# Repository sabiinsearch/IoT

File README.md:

## IoT
Infomation related to Internet of Things (I of Things)

## Code
    - include coding part

## Design
    - include GUI(external) and PCB designs

##  Projects
  - Includes Projects with Internet Of Things

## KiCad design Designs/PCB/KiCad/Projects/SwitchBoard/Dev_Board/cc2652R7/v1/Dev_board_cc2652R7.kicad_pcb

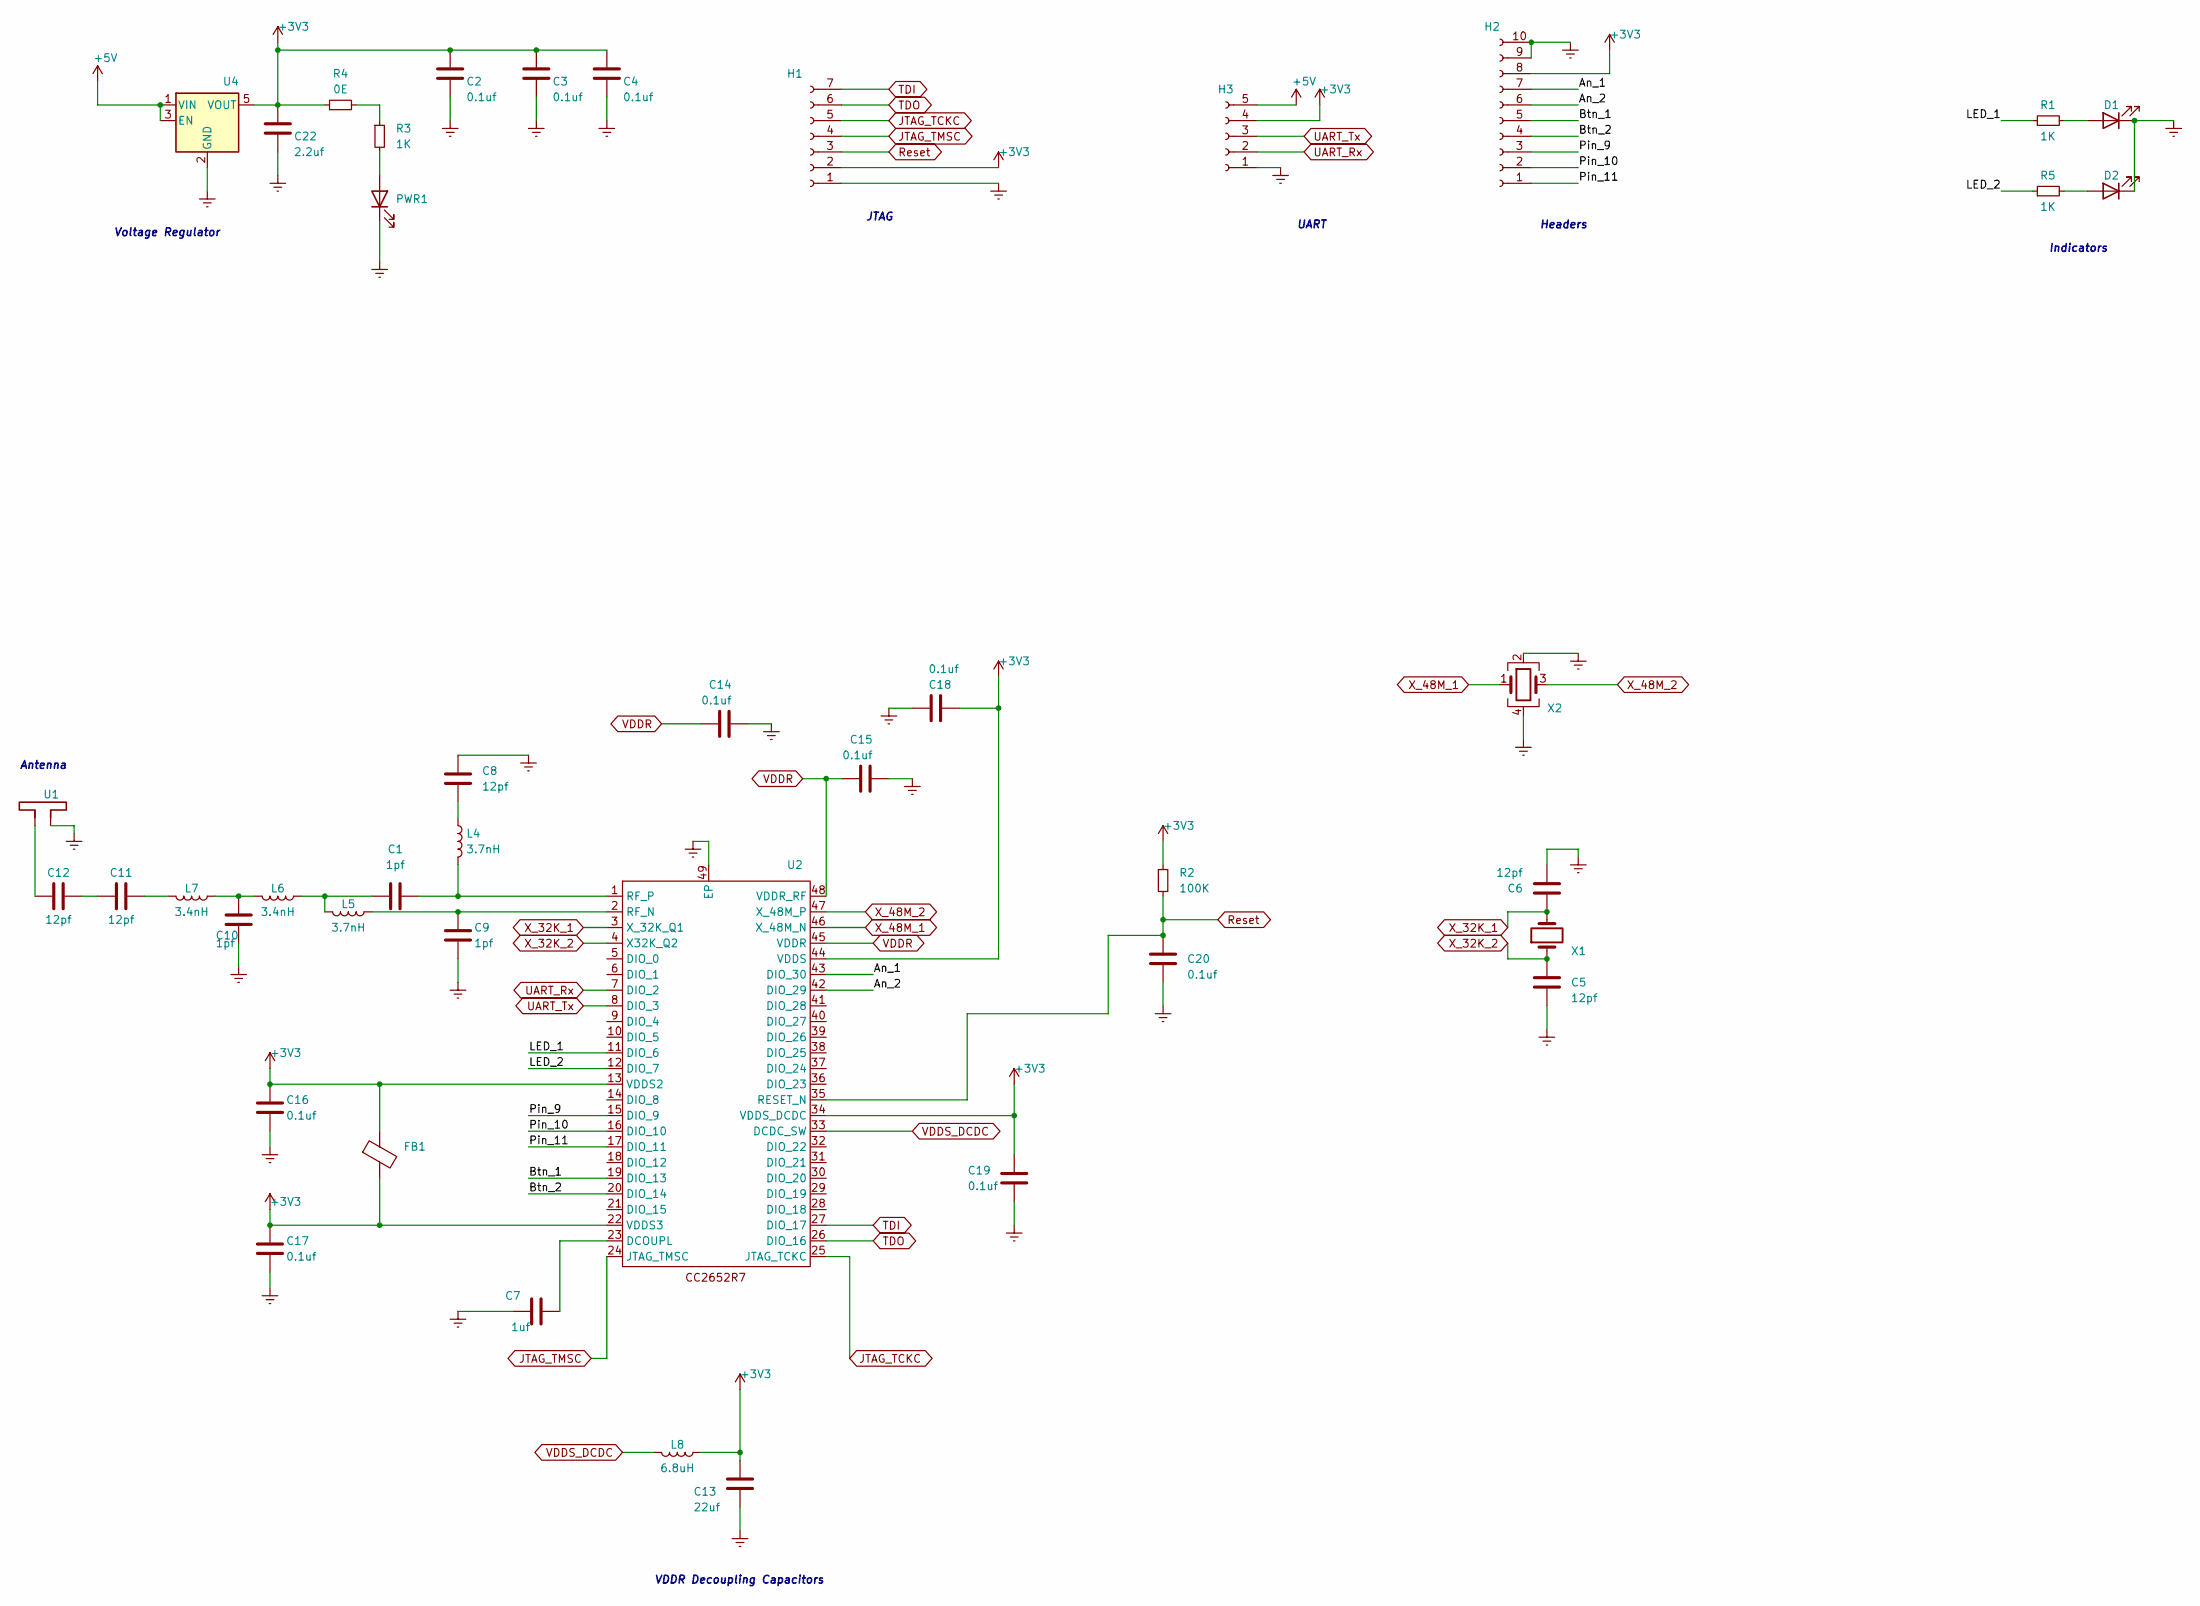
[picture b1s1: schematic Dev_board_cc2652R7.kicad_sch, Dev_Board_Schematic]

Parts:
C1, C9, C10: 1pf; C_0603_1608Metric_Pad1.08x0.95mm_HandSolder
C2, C3, C4, C14, C15, C16, C17, C18, C19, C20: 0.1uf; C_0603_1608Metric_Pad1.08x0.95mm_HandSolder
C5, C6, C8, C11, C12: 12pf; C_0603_1608Metric_Pad1.08x0.95mm_HandSolder
C7: 1uf; C_0603_1608Metric_Pad1.08x0.95mm_HandSolder
C13: 22uf; C_0603_1608Metric_Pad1.08x0.95mm_HandSolder
C22: 2.2uf; C_0603_1608Metric_Pad1.08x0.95mm_HandSolder
D1: LED_1; LED_0603_1608Metric_Pad1.05x0.95mm_HandSolder
D2: LED_2; LED_0603_1608Metric_Pad1.05x0.95mm_HandSolder
FB1: FerriteBead; R_0805_2012Metric_Pad1.20x1.40mm_HandSolder
H1: JTAG_Conn; PinHeader_1x07_P2.54mm_Vertical
H2: Headers; PinHeader_1x10_P2.54mm_Vertical
H3: UART_Conn; PinHeader_1x05_P2.54mm_Vertical
L4, L5: 3.7nH; L_0603_1608Metric_Pad1.05x0.95mm_HandSolder
L6, L7: 3.4nH; L_0603_1608Metric_Pad1.05x0.95mm_HandSolder
L8: 6.8uH; L_0603_1608Metric_Pad1.05x0.95mm_HandSolder
PWR1: LED; LED_0603_1608Metric_Pad1.05x0.95mm_HandSolder
R1, R3, R5: 1K; R_0603_1608Metric_Pad0.98x0.95mm_HandSolder
R2: 100K; R_0603_1608Metric_Pad0.98x0.95mm_HandSolder
R4: 0E; R_0603_1608Metric_Pad0.98x0.95mm_HandSolder
U1: Antenna_Dipole; Texas_SWRA117D_2.4GHz_Left
U2: cc2652R7
U4: AP2112K-3.3; SOT-23-5
X1: 32.768KHz; Crystal_C38-LF_D3.0mm_L8.0mm_Vertical
X2: 48MHz; Crystal_SMD_0603-4Pin_6.0x3.5mm_HandSoldering

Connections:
+3V3: C2.1, C3.1, C4.1, C13.1, C16.1, C17.1, C18.1, C19.1, C22.1, FB1.1, FB1.2, H1.2, H2.8, H3.4, L8.1, R2.1, R4.1, U2.13 (VDDS2), U2.22 (VDDS3), U2.34 (VDDS_DCDC), U2.44 (VDDS), U4.5 (VOUT)
+5V: H3.5, U4.1 (VIN), U4.3 (EN)
/An_1: H2.7, U2.43 (DIO_30)
/An_2: H2.6, U2.42 (DIO_29)
/Btn_1: H2.5, U2.19 (DIO_13)
/Btn_2: H2.4, U2.20 (DIO_14)
/LED_1: R1.1, U2.11 (DIO_6)
/LED_2: R5.1, U2.12 (DIO_7)
/Pin_9: H2.3, U2.15 (DIO_9)
/Pin_10: H2.2, U2.16 (DIO_10)
/Pin_11: H2.1, U2.17 (DIO_11)
GNDREF: C2.2, C3.2, C4.2, C5.2, C6.2, C7.1, C8.1, C9.2, C10.2, C13.2, C14.2, C15.2, C16.2, C17.2, C18.2, C19.2, C20.2, C22.2, D1.1 (K), D2.1 (K), H1.1, H2.9, H2.10, H3.1, PWR1.1 (K), U1.2, U2.49 (EP), U4.2 (GND), X2.2, X2.4; also elsewhere on the board
JTAG_TCKC: H1.5, U2.25 (JTAG_TCKC)
JTAG_TMSC: H1.4, U2.24 (JTAG_TMSC)
unnamed: C1.1, L5.2, L6.1
unnamed: C8.2, L4.1
unnamed: C10.1, L6.2, L7.1
unnamed: C11.1, C12.2
unnamed: C11.2, L7.2
unnamed: C12.1, U1.1
unnamed: D1.2 (A), R1.2
unnamed: D2.2 (A), R5.2
unnamed 22: PWR1.2 (A), R3.2; also elsewhere on the board
unnamed: R3.1, R4.2
unnamed: C7.2, U2.23 (DCOUPL)
unnamed: C9.1, L5.1, U2.2 (RF_N)
unnamed: C1.2, L4.2, U2.1 (RF_P)
Reset: C20.1, H1.3, R2.2, U2.35 (RESET_N)
TDI: H1.7, U2.27 (DIO_17)
TDO: H1.6, U2.26 (DIO_16)
UART_Rx: H3.2, U2.7 (DIO_2)
UART_Tx: H3.3, U2.8 (DIO_3)
VDDR: C14.1, C15.1, U2.45 (VDDR), U2.48 (VDDR_RF)
VDDS_DCDC: L8.2, U2.33 (DCDC_SW)
X_32K_1: C6.1, U2.3 (X_32K_Q1), X1.2
X_32K_2: C5.1, U2.4 (X32K_Q2), X1.1
X_48M_1: U2.46 (X_48M_N), X2.1
X_48M_2: U2.47 (X_48M_P), X2.3

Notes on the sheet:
Antenna
JTAG
VDDR Decoupling Capacitors
Headers
Voltage Regulator
Indicators
UART

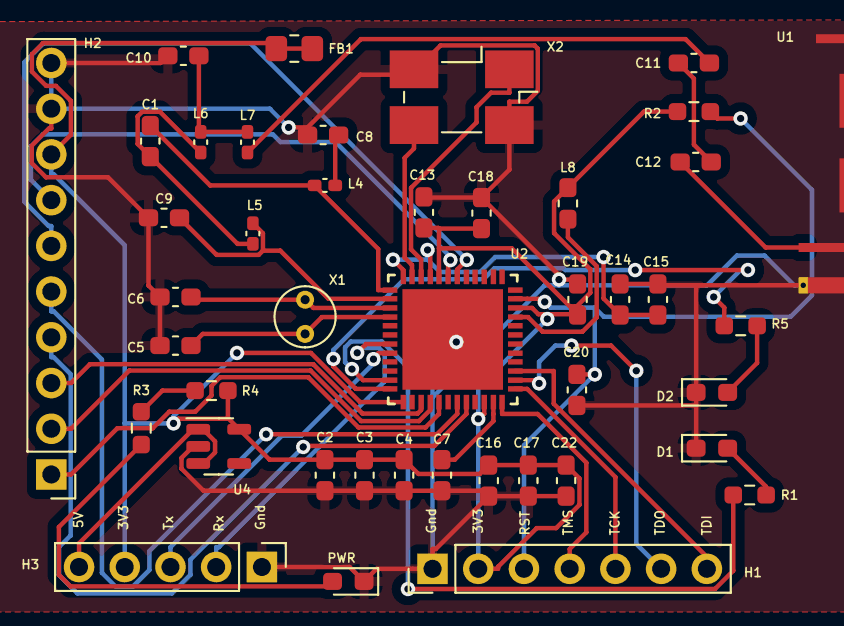
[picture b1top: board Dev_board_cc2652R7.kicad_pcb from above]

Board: 2 copper layers, 43 parts (0 on the bottom side), 38 nets.

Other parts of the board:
PWR: LED; LED_0603_1608Metric_Pad1.05x0.95mm_HandSolder

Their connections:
GNDREF: PWR.1 (K); also elsewhere on the board
unnamed 22: PWR.2 (A); also elsewhere on the board

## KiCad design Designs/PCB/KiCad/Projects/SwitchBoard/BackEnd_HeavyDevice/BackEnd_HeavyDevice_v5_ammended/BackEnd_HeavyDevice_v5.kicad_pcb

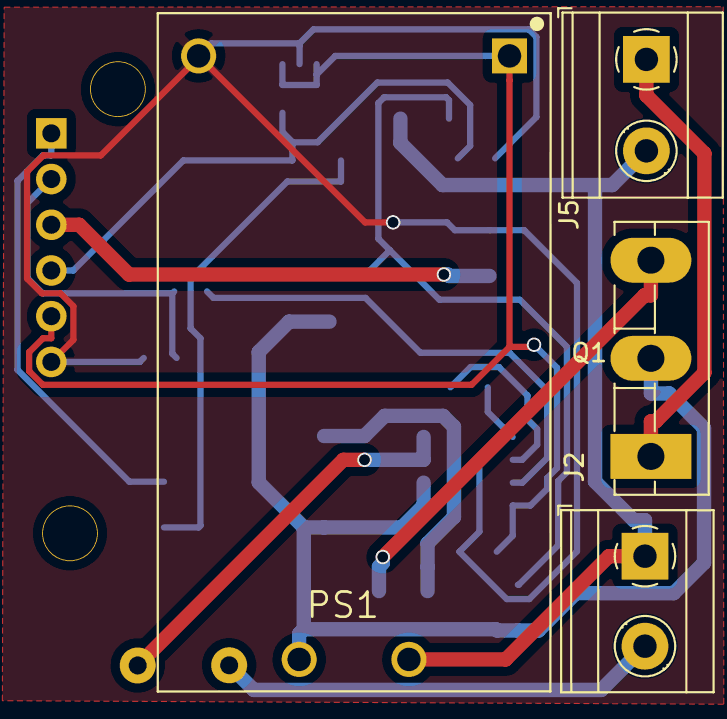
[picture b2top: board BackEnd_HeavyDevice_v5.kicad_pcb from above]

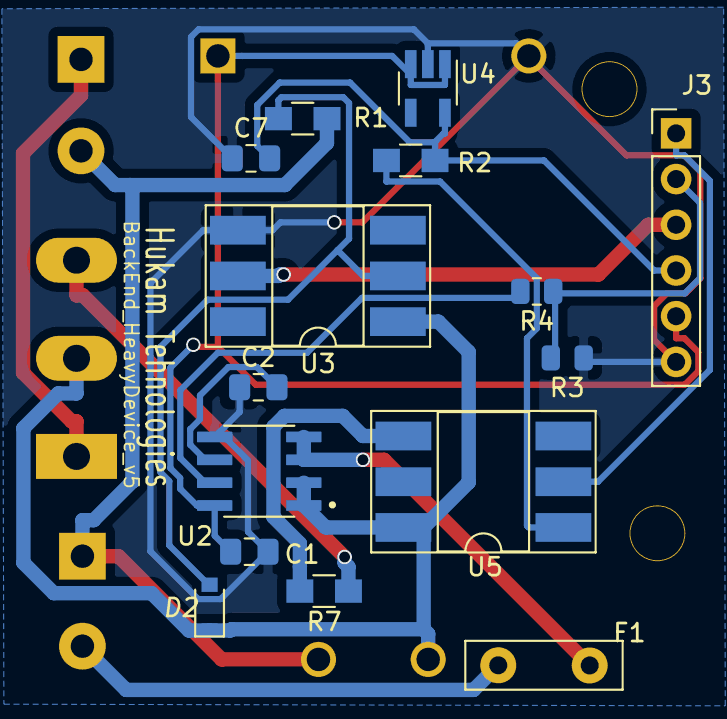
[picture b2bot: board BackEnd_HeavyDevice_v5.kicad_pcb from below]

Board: 2 copper layers, 21 parts (15 on the bottom side), 17 nets.

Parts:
C1: 100nf; C_0805_2012Metric_Pad1.18x1.45mm_HandSolder
C2: 1nf; C_0805_2012Metric_Pad1.18x1.45mm_HandSolder
C7: 2.2uf; C_0805_2012Metric_Pad1.18x1.45mm_HandSolder
D2: IN14007; D_0805
F1: Fuse_Small; Fuse_TE5_Littlefuse-395Series
J2: Screw_Terminal_01x02; TerminalBlock_Phoenix_MKDS-1,5-2_1x02_P5.00mm_Horizontal
J3: Conn_01x06_Female; PinHeader_1x06_P2.54mm_Vertical
J5: Screw_Terminal_01x02; TerminalBlock_Phoenix_MKDS-1,5-2-5.08_1x02_P5.08mm_Horizont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
M1, M2: MountingHole_2.1mm; MountingHole_2.5mm
PS1: HLK-PM01; 277
Q1: BT136-500; GN27120BN
R1: 220K; R_0805_HandSoldering
R2: 100E; R_0805_HandSoldering
R3, R4: 5K; R_0805_2012Metric
R7: 470E; R_0805_HandSoldering
U2: ACS712-20; ACS712_20
U3: 4N35; DIP-6_W8.89mm_SMDSocket_LongPads
U4: AP2112K-3.3; SOT-23-5_HandSoldering
U5: MOC3021; DIP-6_W8.89mm_SMDSocket_LongPads

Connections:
/3.3V: C7.2, J3.4, R2.2, U4.5
/5V: C1.1, J3.5, PS1.5, U2.8, U4.1, U4.3
/DSW1: J3.1, U5.2
/Energy_frmSensor: R4.2, U2.7
/Energy_toStm: J3.2, R3.2, R4.1
/GND: C1.2, C2.1, C7.1, J3.6, PS1.4, R3.1, U2.5, U3.4, U4.2
/Mains_Live_In: F1.1, J2.2
/Mains_Live_Out: D2.1, PS1.2, Q1.2, U2.1, U2.2, U3.1, U5.6
/Mains_Neutral: J2.1, J5.2, PS1.1, R1.2
/Opto_In: J3.3, U3.5
/Out1: J5.1, Q1.1
unnamed: C2.2, U2.6
unnamed: D2.2, R1.1, U3.2
unnamed: F1.2, U2.3, U2.4
unnamed: Q1.3, R7.1
unnamed: R2.1, U5.1
unnamed: R7.2, U5.4

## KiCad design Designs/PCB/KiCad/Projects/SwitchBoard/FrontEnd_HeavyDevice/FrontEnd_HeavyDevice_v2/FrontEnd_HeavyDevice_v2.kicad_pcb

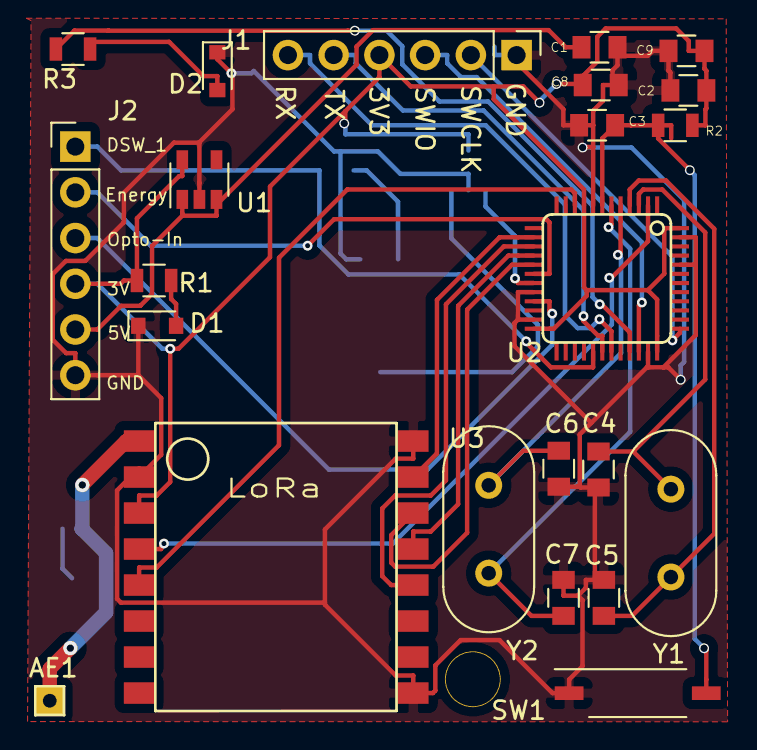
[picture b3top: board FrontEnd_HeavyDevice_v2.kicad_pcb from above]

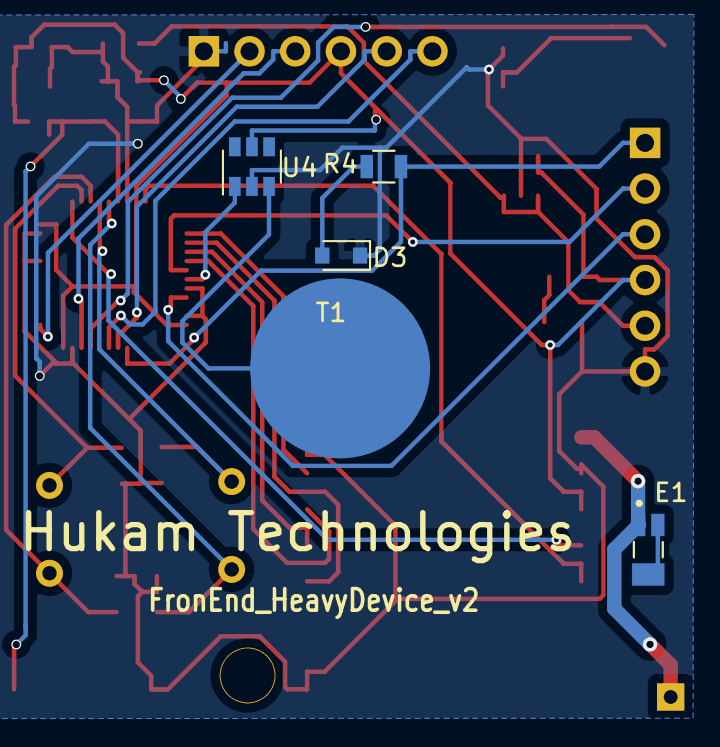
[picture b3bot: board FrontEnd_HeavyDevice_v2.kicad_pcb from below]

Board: 2 copper layers, 29 parts (5 on the bottom side), 29 nets.

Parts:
AE1: Antenna; Anntenna
C1, C2, C8: 100 nf; C_0805
C3: 1.0uf; C_0805
C4, C5: 10pf; C_0805
C6, C7: 20pf; C_0805
C9: 10uf; C_0805
D1, D2, D3: LED; D_0805
E1: YC0009AA; XCVR_YC0009AA
J1: Conn_01x06_Female; Pin_Header_Straight_1x06_Pitch2.54mm
J2: Conn_01x06_Female; PinHeader_1x06_P2.54mm_Vertical
M2: MountingHole_2.1mm; MountingHole_2.5mm
R1, R3, R4: 510 R; R_0805
R2: 10K; R_0805
SW1: SW_Push; SW_DIP_x1_W7.62mm_Slide_Copal_CHS-B
T1: Touch_Pad
U1: APK2112.K-3.3; SOT-23-5
U2: STM32; STM32(LQFP48)
U3: LoRa
U4: TTP223; SOT-23-6
Y1: 32.768K; Crystal_HC49-4H_Vertical
Y2: 32Mhz; Crystal_HC49-4H_Vertical

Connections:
/5V: C1.2, J2.5, U1.1, U1.3
/DIO0: U2.10, U3.5
/DSW_1: J2.1, R4.2, U2.29
/Energy: J2.2, U2.18
/GND: C1.1, C2.1, C3.1, C4.2, C5.2, C6.2, C7.2, C8.1, C9.1, D1.1, D2.1, D3.1, J1.1, J2.6, SW1.1, U1.2, U2.8, U2.20, U2.23, U2.35, U2.44, U2.47, U3.2, U3.9, U3.16, U4.2
/MISO: U2.16, U3.13
/MOSI: U2.17, U3.14
/NSS: U2.14, U3.15
/OSCIN: C6.1, U2.5, Y2.1
/OSCOUT: C7.1, U2.6, Y2.2
/Opto_IN: J2.3, U2.21
/PC14: C4.1, U2.3, Y1.1
/PC15: C5.1, U2.4, Y1.2
/RESET: C3.2, R2.2, SW1.2, U2.7
/RX0: J1.6, U2.31
/Reset_Lora: U2.2, U3.4
/SCK: U2.15, U3.12
/SWCLK: J1.2, U2.37
/SWIO: J1.3, U2.34
/TX0: J1.5, U2.30
/Touch_1: U2.19, U4.1
/VCC3V3: C2.2, C8.2, C9.2, J1.4, J2.4, R1.2, R2.1, U1.5, U2.9, U2.24, U2.36, U2.48, U3.3, U4.5
unnamed: AE1.1, E1.1, U3.1
unnamed: D1.2, R1.1
unnamed: D2.2, R3.1
unnamed: D3.2, R4.1
unnamed: E1.2, E1.3
unnamed: R3.2, U2.33
unnamed: T1.1, U4.3

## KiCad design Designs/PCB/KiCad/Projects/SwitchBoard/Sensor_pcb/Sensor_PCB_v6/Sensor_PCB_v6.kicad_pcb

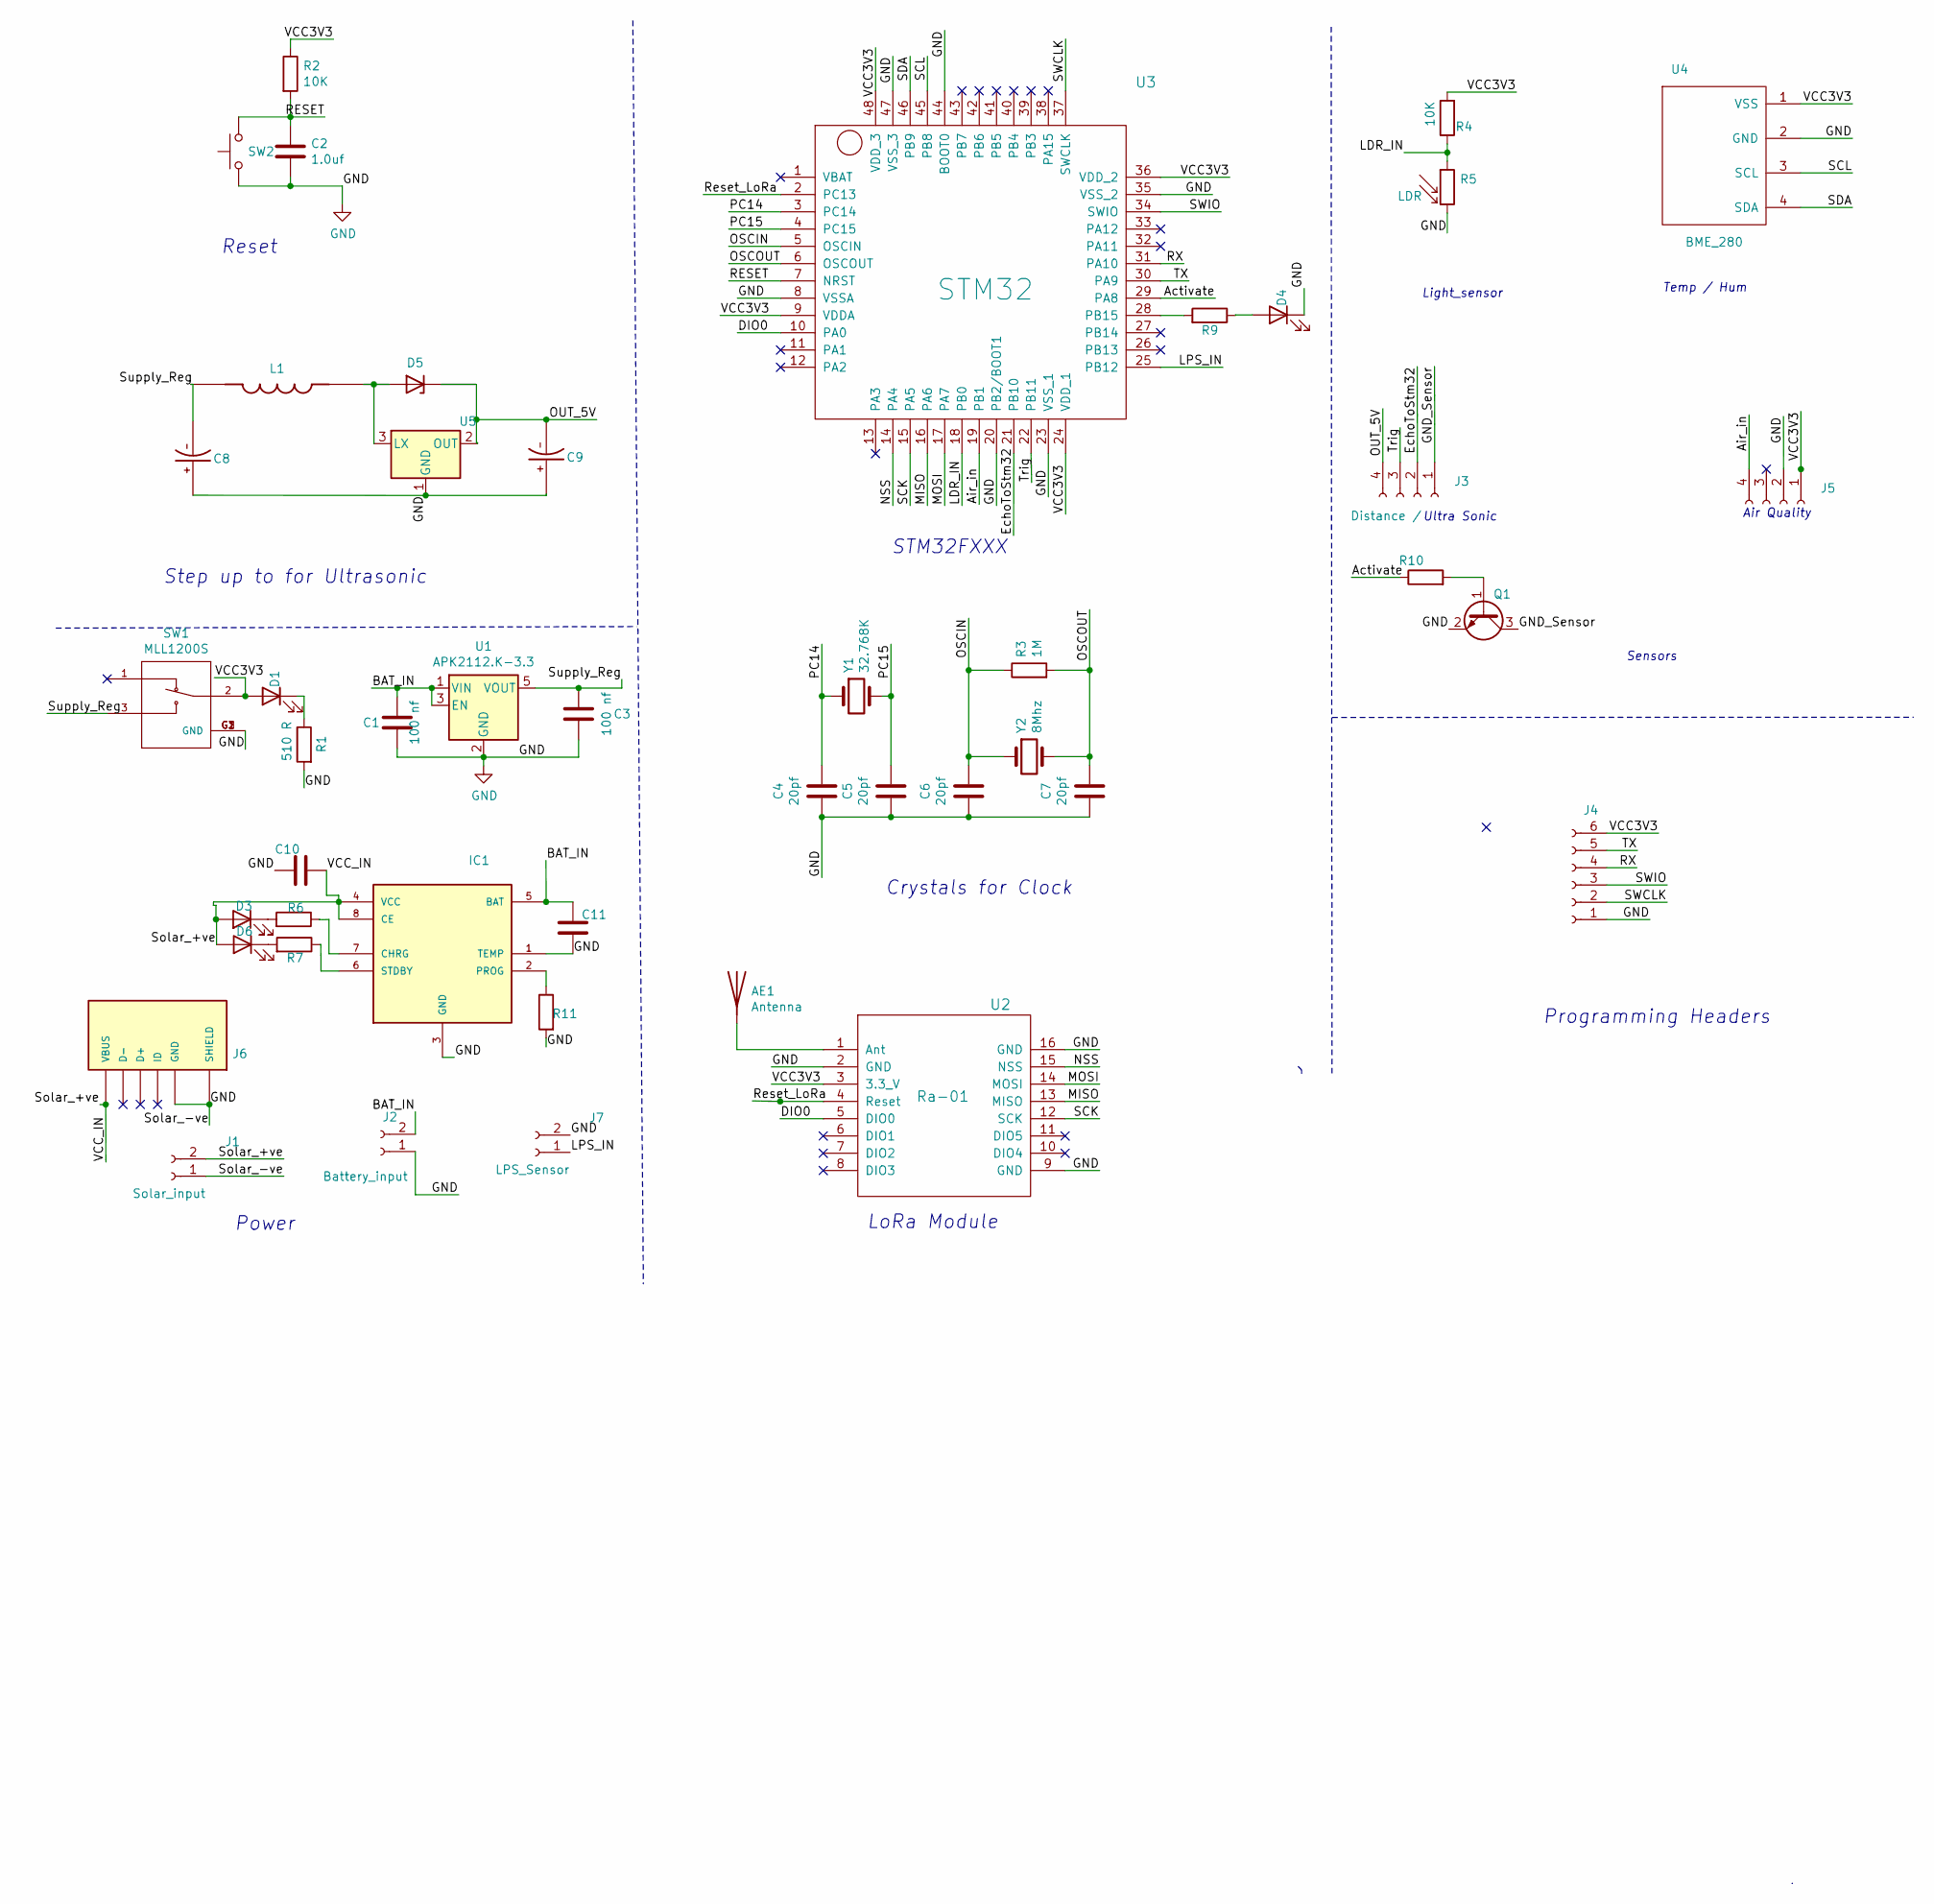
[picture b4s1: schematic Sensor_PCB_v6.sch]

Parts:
AE1: Antenna; Pin_Header_Straight_1x01_Pitch2.54mm
C1, C3: 100 nf; C_0805
C2: 1.0uf; C_0805
C4, C5, C6, C7: 20pf; C_0805
C8, C9: 100 uF; CAPAE660X550N
C10, C11: 10uf; C_0805
D1, D3, D6: Pwr_L.E.D; D_0805
D4: Bat_Low; D_0805
D5: SS14; D_1206
IC1: TP4056; SOP-8
J1: Solar_input; Battery_holder
J2: Battery_input; Battery_holder
J3: Distance /; Pin_Header_Straight_1x04_Pitch2.54mm
J4: Conn_01x06_Female; Pin_Header_Straight_1x06_Pitch2.54mm
J5: Airquality; Pin_Header_Straight_1x04_Pitch2.54mm
J6: USB3130-XX-X_REVD; Conn_USBmicro-B_ebay-side_TH
J7: LPS_Sensor; Battery_holder
L1: Inductor_22uH; IND_22uH
Q1: BC547
R1, R9: 510 R; R_0805
R2, R4: 10K; R_0805
R3: 1M; R_0805
R5: LDR; D_A-405_P5.08mm_Vertical_AnodeUp
R6, R7, R10: 1K; R_0805
R11: 510R; R_0805
SW1: MLL1200S; SW_MLL1200S
SW2: SW_Push; SW_PUSH_6mm_h5mm
U1: APK2112.K-3.3; SOT-23-5
U2: Ra-01; LoRa
U3: STM32; STM32(LQFP48)
U4: BME_280; BME280
U5: BL8530; SOT89
Y1: 32.768K; Crystal_HC49-4H_Vertical
Y2: 8Mhz; Crystal_HC49-4H_Vertical

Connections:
/Activate: R10.1, U3.29 (PA8)
/Air_in: J5.4, U3.19 (PB1)
/BAT_IN: C1.2, C11.2, IC1.5 (BAT), J2.2, U1.1 (VIN), U1.3 (EN)
/DIO0: U2.5 (DIO0), U3.10 (PA0)
/EchoToStm32: J3.2, U3.21 (PB10)
/GND: C1.1, C2.1, C3.1, C4.2, C5.2, C6.2, C7.2, C8.1, C9.1, C10.2, C11.1, D4.1 (K), IC1.1 (TEMP), IC1.3 (GND), J1.1, J2.1, J4.1, J5.2, J6.5 (GND), J6.6 (SHIELD), J7.2, Q1.2 (E), R1.2, R5.2, R11.2, SW1.G1 (GND), SW1.G2 (GND), SW1.G3 (GND), SW2.1, U1.2 (GND), U2.2 (GND), U2.9 (GND), U2.16 (GND), U3.8 (VSSA), U3.20 (PB2/BOOT1), U3.23 (VSS_1), U3.35 (VSS_2), U3.44 (BOOT0), U3.47 (VSS_3), U4.2 (GND), U5.1 (GND)
/GND_Sensor: J3.1, Q1.3 (C)
/LDR_IN: R4.1, R5.1, U3.18 (PB0)
/LPS_IN: J7.1, U3.25 (PB12)
/MISO: U2.13 (MISO), U3.16 (PA6)
/MOSI: U2.14 (MOSI), U3.17 (PA7)
/NSS: U2.15 (NSS), U3.14 (PA4)
/OSCIN: C6.1, R3.1, U3.5 (OSCIN), Y2.1
/OSCOUT: C7.1, R3.2, U3.6 (OSCOUT), Y2.2
/OUT_5V: C9.2, D5.1 (K), J3.4, U5.2 (OUT)
/PC14: C4.1, U3.3 (PC14), Y1.1
/PC15: C5.1, U3.4 (PC15), Y1.2
/RESET: C2.2, R2.2, SW2.2, U3.7 (NRST)
/RX: J4.4, U3.31 (PA10)
/Reset_LoRa: U2.4 (Reset), U3.2 (PC13)
/SCK: U2.12 (SCK), U3.15 (PA5)
/SCL: U3.45 (PB8), U4.3 (SCL)
/SDA: U3.46 (PB9), U4.4 (SDA)
/SWCLK: J4.2, U3.37 (SWCLK)
/SWIO: J4.3, U3.34 (SWIO)
/Solar_+ve: C10.1, D3.2 (A), D6.2 (A), IC1.4 (VCC), IC1.8 (CE), J1.2, J6.1 (VBUS)
/Supply_Reg: C3.2, C8.2, L1.1, SW1.3, U1.5 (VOUT)
/TX: J4.5, U3.30 (PA9)
/Trig: J3.3, U3.22 (PB11)
/VCC3V3: D1.2 (A), J4.6, J5.1, R2.1, R4.2, SW1.2, U2.3 (3.3_V), U3.9 (VDDA), U3.24 (VDD_1), U3.36 (VDD_2), U3.48 (VDD_3), U4.1 (VSS)
unnamed: AE1.1, U2.1 (Ant)
unnamed: D1.1 (K), R1.1
unnamed: D3.1 (K), R6.2
unnamed: D4.2 (A), R9.1
unnamed: D5.2 (A), L1.2, U5.3 (LX)
unnamed: D6.1 (K), R7.2
unnamed: IC1.2 (PROG), R11.1
unnamed: IC1.6 (STDBY), R7.1
unnamed: IC1.7 (CHRG), R6.1
unnamed: Q1.1 (B), R10.2
unnamed: R9.2, U3.28 (PB15)

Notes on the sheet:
Programming Headers
Power
Reset
LoRa Module
Sensors
Temp / Hum
Light_sensor
Air Quality
STM32FXXX
Crystals for Clock
Ultra Sonic
Step up to for Ultrasonic

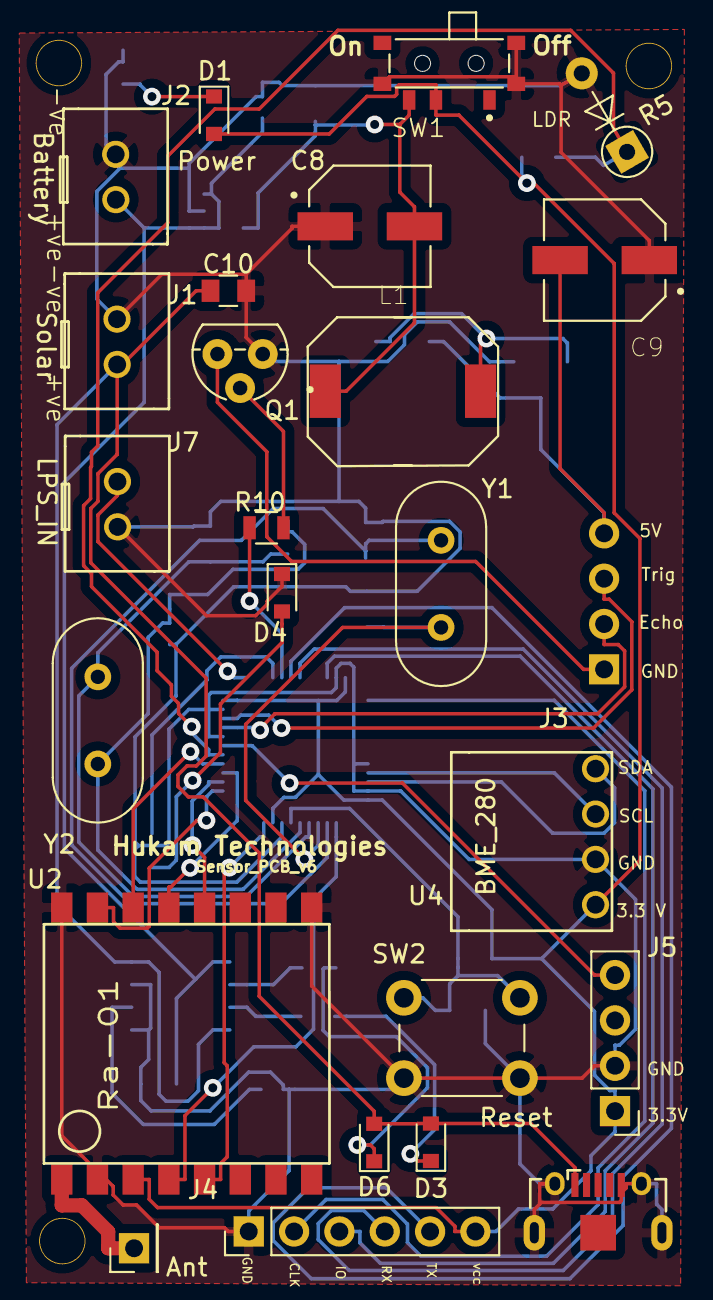
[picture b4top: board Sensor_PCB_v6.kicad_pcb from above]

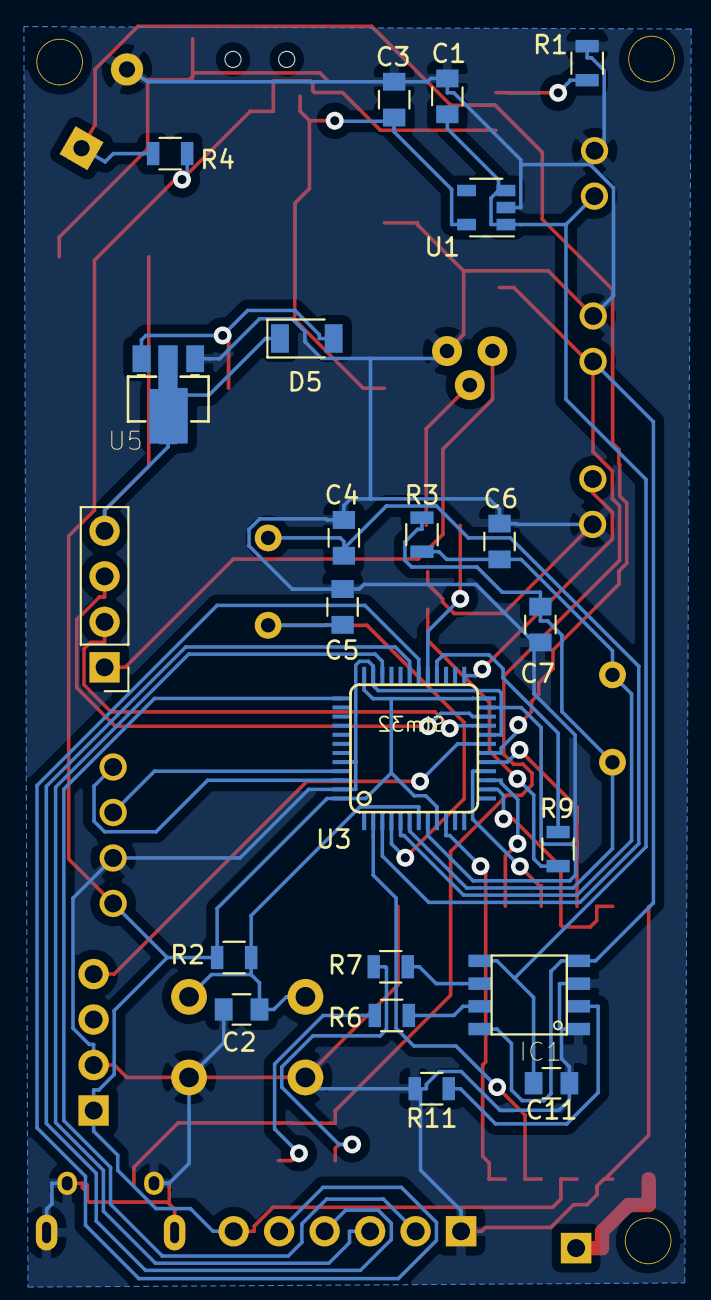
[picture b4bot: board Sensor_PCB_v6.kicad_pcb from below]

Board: 2 copper layers, 49 parts (22 on the bottom side), 41 nets.

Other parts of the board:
M1, M2, M3: MountingHole_2.1mm; MountingHole_2.5mm

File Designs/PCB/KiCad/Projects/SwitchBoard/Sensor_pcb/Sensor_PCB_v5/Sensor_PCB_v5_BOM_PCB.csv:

"Id";"Designator";"Package";"Quantity";"Designation";"Supplier and ref";
1;"M3,M2,M1";"MountingHole1.5mm";3;"MountingHole_2.1mm";;;
2;"IC1";"SOP-8";1;"TP4056";;;
3;"J7";"Battery_holder";1;"LPS_Sensor";;;
4;"L1";"IND_22uH";1;"Inductor_22uH";;;
5;"C8,C9";"CAPAE660X550N";2;"100 uF";;;
6;"J6";"Conn_USBmicro-B_ebay-side_TH";1;"USB3130-XX-X_REVD";;;
7;"J2";"Battery_holder";1;"Battery_input";;;
8;"J1";"Battery_holder";1;"Solar_input";;;
9;"U4";"BME280";1;"BME_280";;;
10;"U5";"SOT89";1;"BL8530";;;
11;"J4";"Pin_Header_Straight_1x06_Pitch2.54mm";1;"Conn_01x06_Female";;;
12;"U3";"STM32(LQFP48)";1;"STM32";;;
13;"SW1";"SW_MLL1200S";1;"MLL1200S";;;
14;"R9,R1";"R_0805";2;"510 R";;;
15;"D4";"D_0805";1;"Bat_Low";;;
16;"J5";"Pin_Header_Straight_1x04_Pitch2.54mm";1;"Airquality";;;
17;"U2";"LoRa";1;"Ra-01";;;
18;"AE1";"Pin_Header_Straight_1x01_Pitch2.54mm";1;"Antenna";;;
19;"J3";"Pin_Header_Straight_1x04_Pitch2.54mm";1;"Distance /";;;
20;"C2";"C_0805";1;"1.0uf";;;
21;"C4,C5,C6,C7";"C_0805";4;"20pf";;;
22;"C1,C3";"C_0805";2;"100 nf";;;
23;"D1,D3,D6";"D_0805";3;"Pwr_L.E.D";;;
24;"R2,R4";"R_0805";2;"10K";;;
25;"R3";"R_0805";1;"1M";;;
26;"R5";"D_A-405_P5.08mm_Vertical_AnodeUp";1;"LDR";;;
27;"U1";"SOT-23-5";1;"APK2112.K-3.3";;;
28;"Y1";"Crystal_HC49-4H_Vertical";1;"32.768K";;;
29;"Y2";"Crystal_HC49-4H_Vertical";1;"8Mhz";;;
30;"SW2";"SW_PUSH_6mm_h5mm";1;"SW_Push";;;
31;"D5";"D_1206";1;"SS14";;;
32;"C10,C11";"C_0805";2;"10uf";;;
33;"Q1";"BC547-SOT23";1;"BC547";;;
34;"R6,R7,R10";"R_0805";3;"1K";;;
35;"R11";"R_0805";1;"510R";;;
